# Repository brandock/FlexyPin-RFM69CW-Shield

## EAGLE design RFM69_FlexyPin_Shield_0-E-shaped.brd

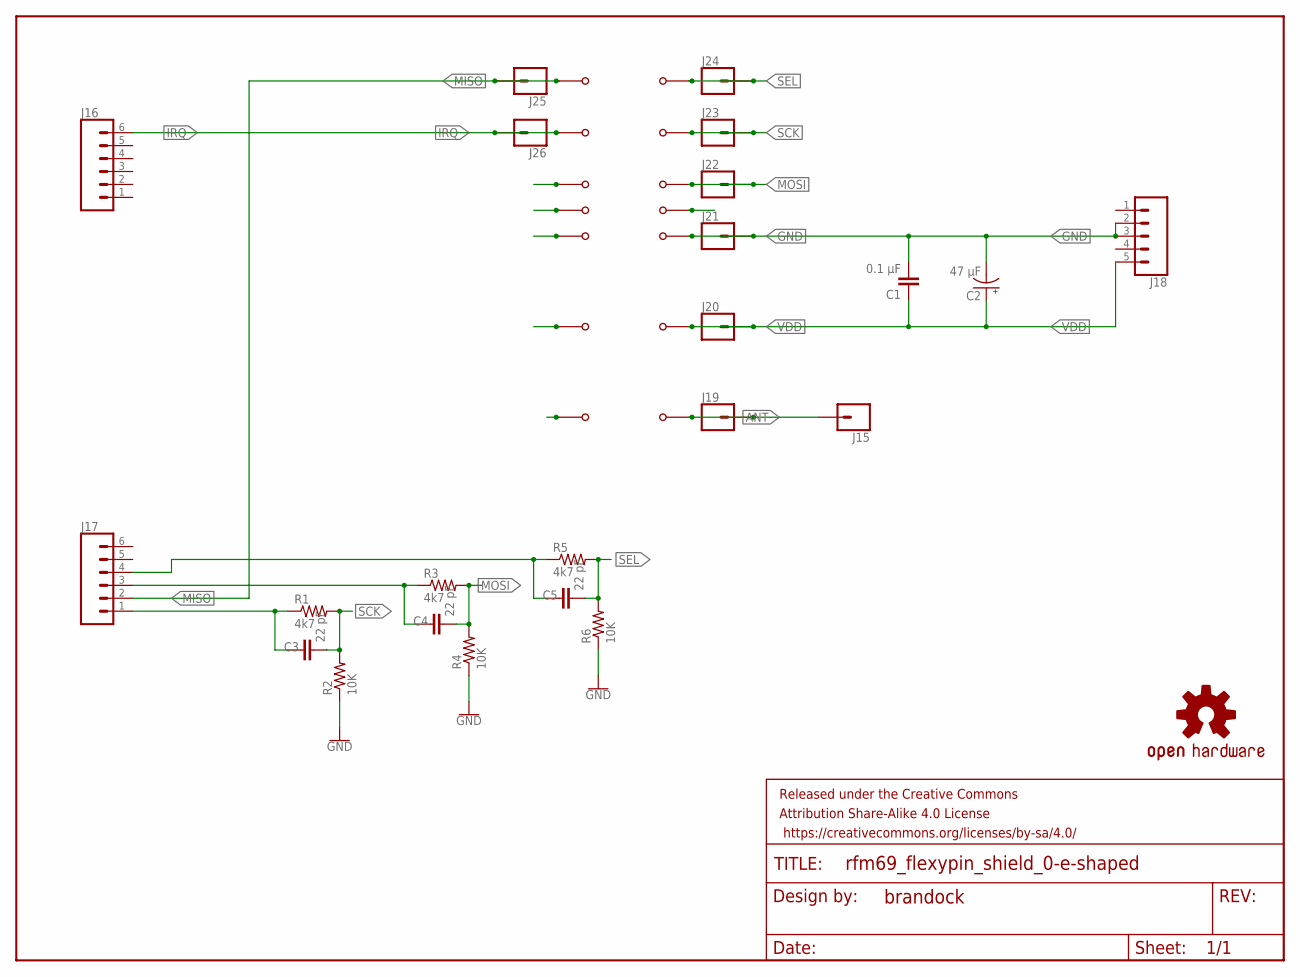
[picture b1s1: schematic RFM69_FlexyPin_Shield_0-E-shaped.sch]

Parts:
C1: 0.1 µF; C025-024X044
C2: 47 µF; E2,5-6
C3, C4, C5: 22 pF; C025-024X044
FRAME1: FRAME-LETTERNO_PACKAGE; DUMMY
J1, J2, J3, J4, J5, J6, J7, J8, J9, J10, J11, J12, J13, J14: FLEXYPIN
J15, J19, J20, J21, J22, J23, J24, J25, J26: CONN_01PTH_NO_SILK_YES_STOP; 1X01_NO_SILK
J16, J17: CONN_06LOCK; 1X06_LOCK
J18: CONN_05LOCK; 1X05_LOCK
LOGO1: OSHW-LOGOL; OSHW-LOGO-L
R1, R3, R5: 4k7; 0204/7
R2, R4, R6: 10K; 0204/7

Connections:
ANT: J14.P$1, J15.1, J19.1
GND: C1.2, C2.-, J12.P$1, J18.2, J18.3, J21.1, R2.1, R4.1, R6.1
IRQ: J2.P$1, J16.6, J26.1
MISO: J1.P$1, J17.2, J25.1
MOSI: C4.2, J10.P$1, J22.1, R3.2, R4.2
unnamed: C3.1, J17.1, R1.1
unnamed: C4.1, J17.3, R3.1
unnamed: C5.1, J17.4, R5.1
SCK: C3.2, J9.P$1, J23.1, R1.2, R2.2
SEL: C5.2, J8.P$1, J24.1, R5.2, R6.2
VDD: C1.1, C2.+, J13.P$1, J18.5, J20.1

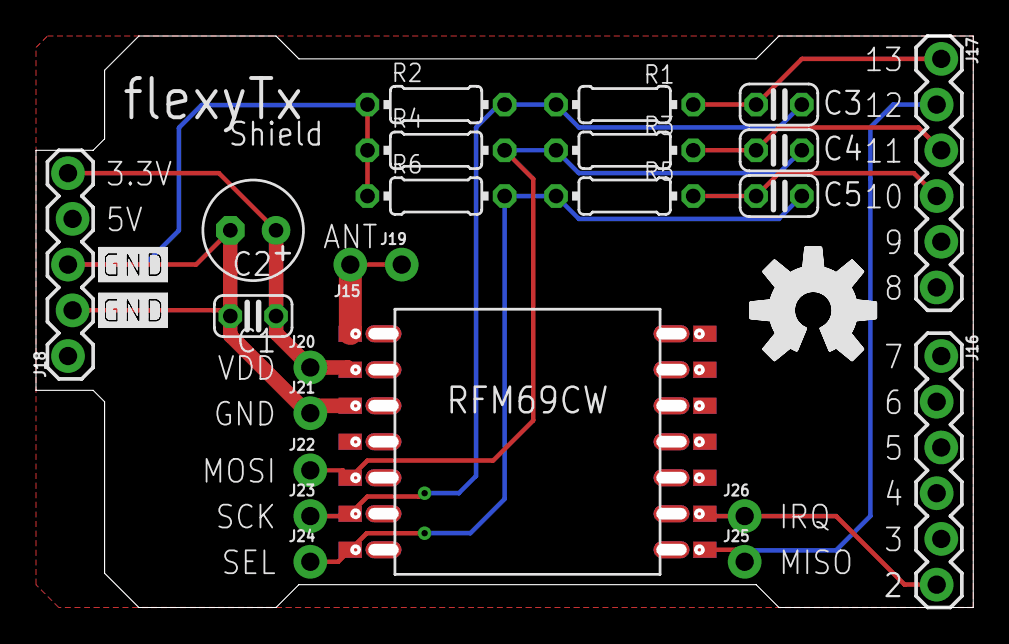
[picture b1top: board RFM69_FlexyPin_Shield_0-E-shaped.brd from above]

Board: 2 copper layers, 51.4 x 31.1 mm, 40 parts (0 on the bottom side), 11 nets.

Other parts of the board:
LOGO2: OSHW-LOGOL; OSHW-LOGO-L

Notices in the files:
parts and their libraries:
SparkFun-Aesthetics: Licensing: Creative Commons ShareAlike 4.0 International - https://creativecommons.org/licenses/by-sa/4.0
SparkFun-Aesthetics: Released under the Creative Commons Attribution Share-Alike 4.0 License
SparkFun-Aesthetics: https://creativecommons.org/licenses/by-sa/4.0
